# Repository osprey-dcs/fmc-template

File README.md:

# RF Input FMC

A single width HPC FMC board which brings in two high frequency (RF) clocks to
to MGT capable pins when matched with the [LBL Marble](https://github.com/BerkeleyLab/Marble) FMC carrier.

This design is Open Hardware created by Osprey DCS and published under the terms of the
[CERN Open Hardware Licence Version 2 - Strongly Reciprocal](cern_ohl_s_v2.txt) license.

This repository contains KiCad 9 design files.

- [Current generated](https://osprey-dcs.github.io/fmc-template/)
  - [Schematic](https://osprey-dcs.github.io/fmc-template/fmc-template-schematic.pdf)
  - [BoM](https://osprey-dcs.github.io/fmc-template/fmc-template-bom.csv)
  - [STeP model](https://osprey-dcs.github.io/fmc-template/3D/fmc-template-3D.step)

## Status

Incomplete, under development, and not yet produced.

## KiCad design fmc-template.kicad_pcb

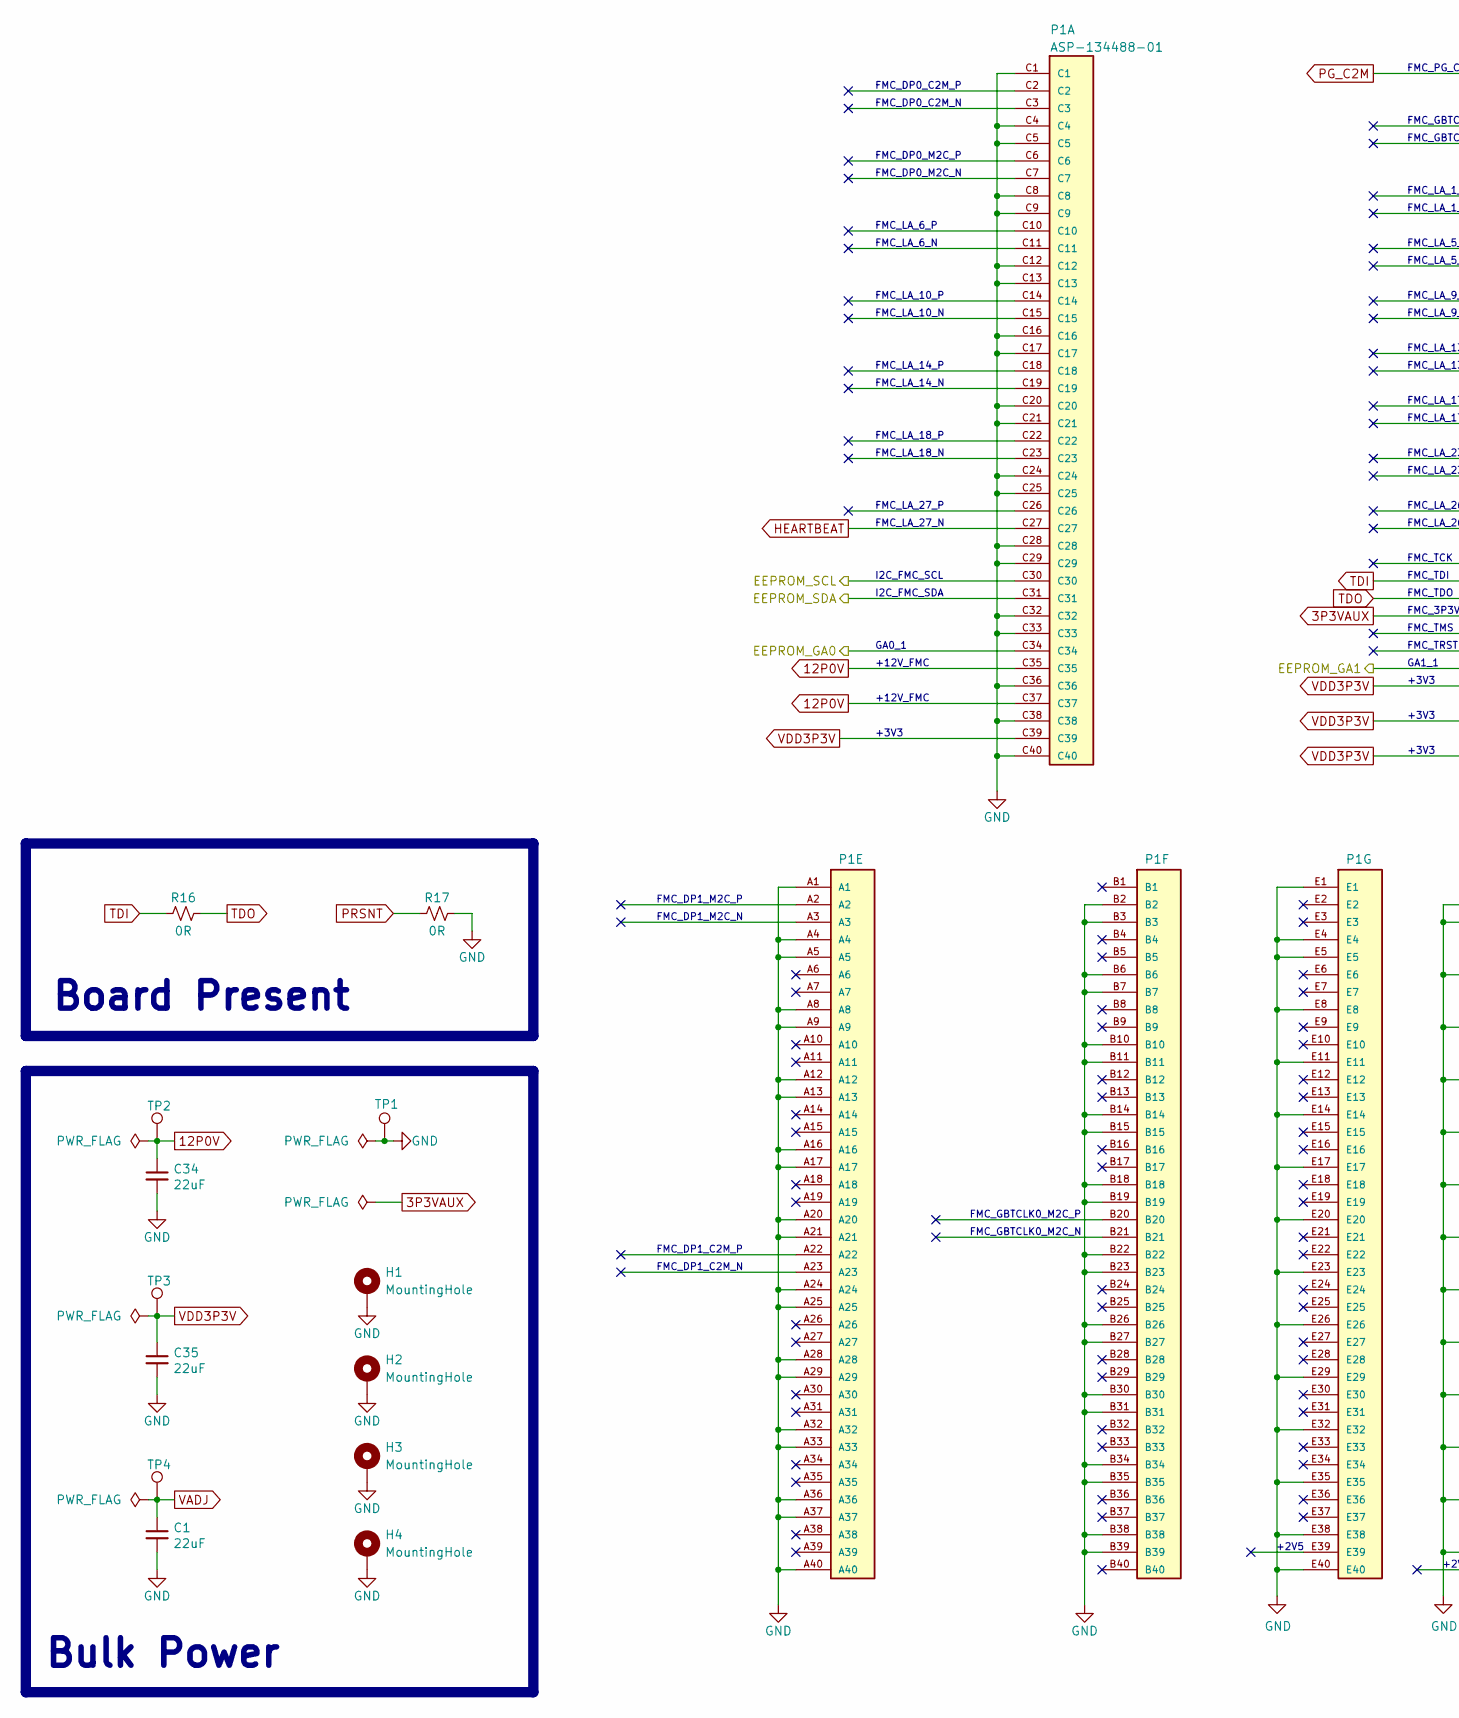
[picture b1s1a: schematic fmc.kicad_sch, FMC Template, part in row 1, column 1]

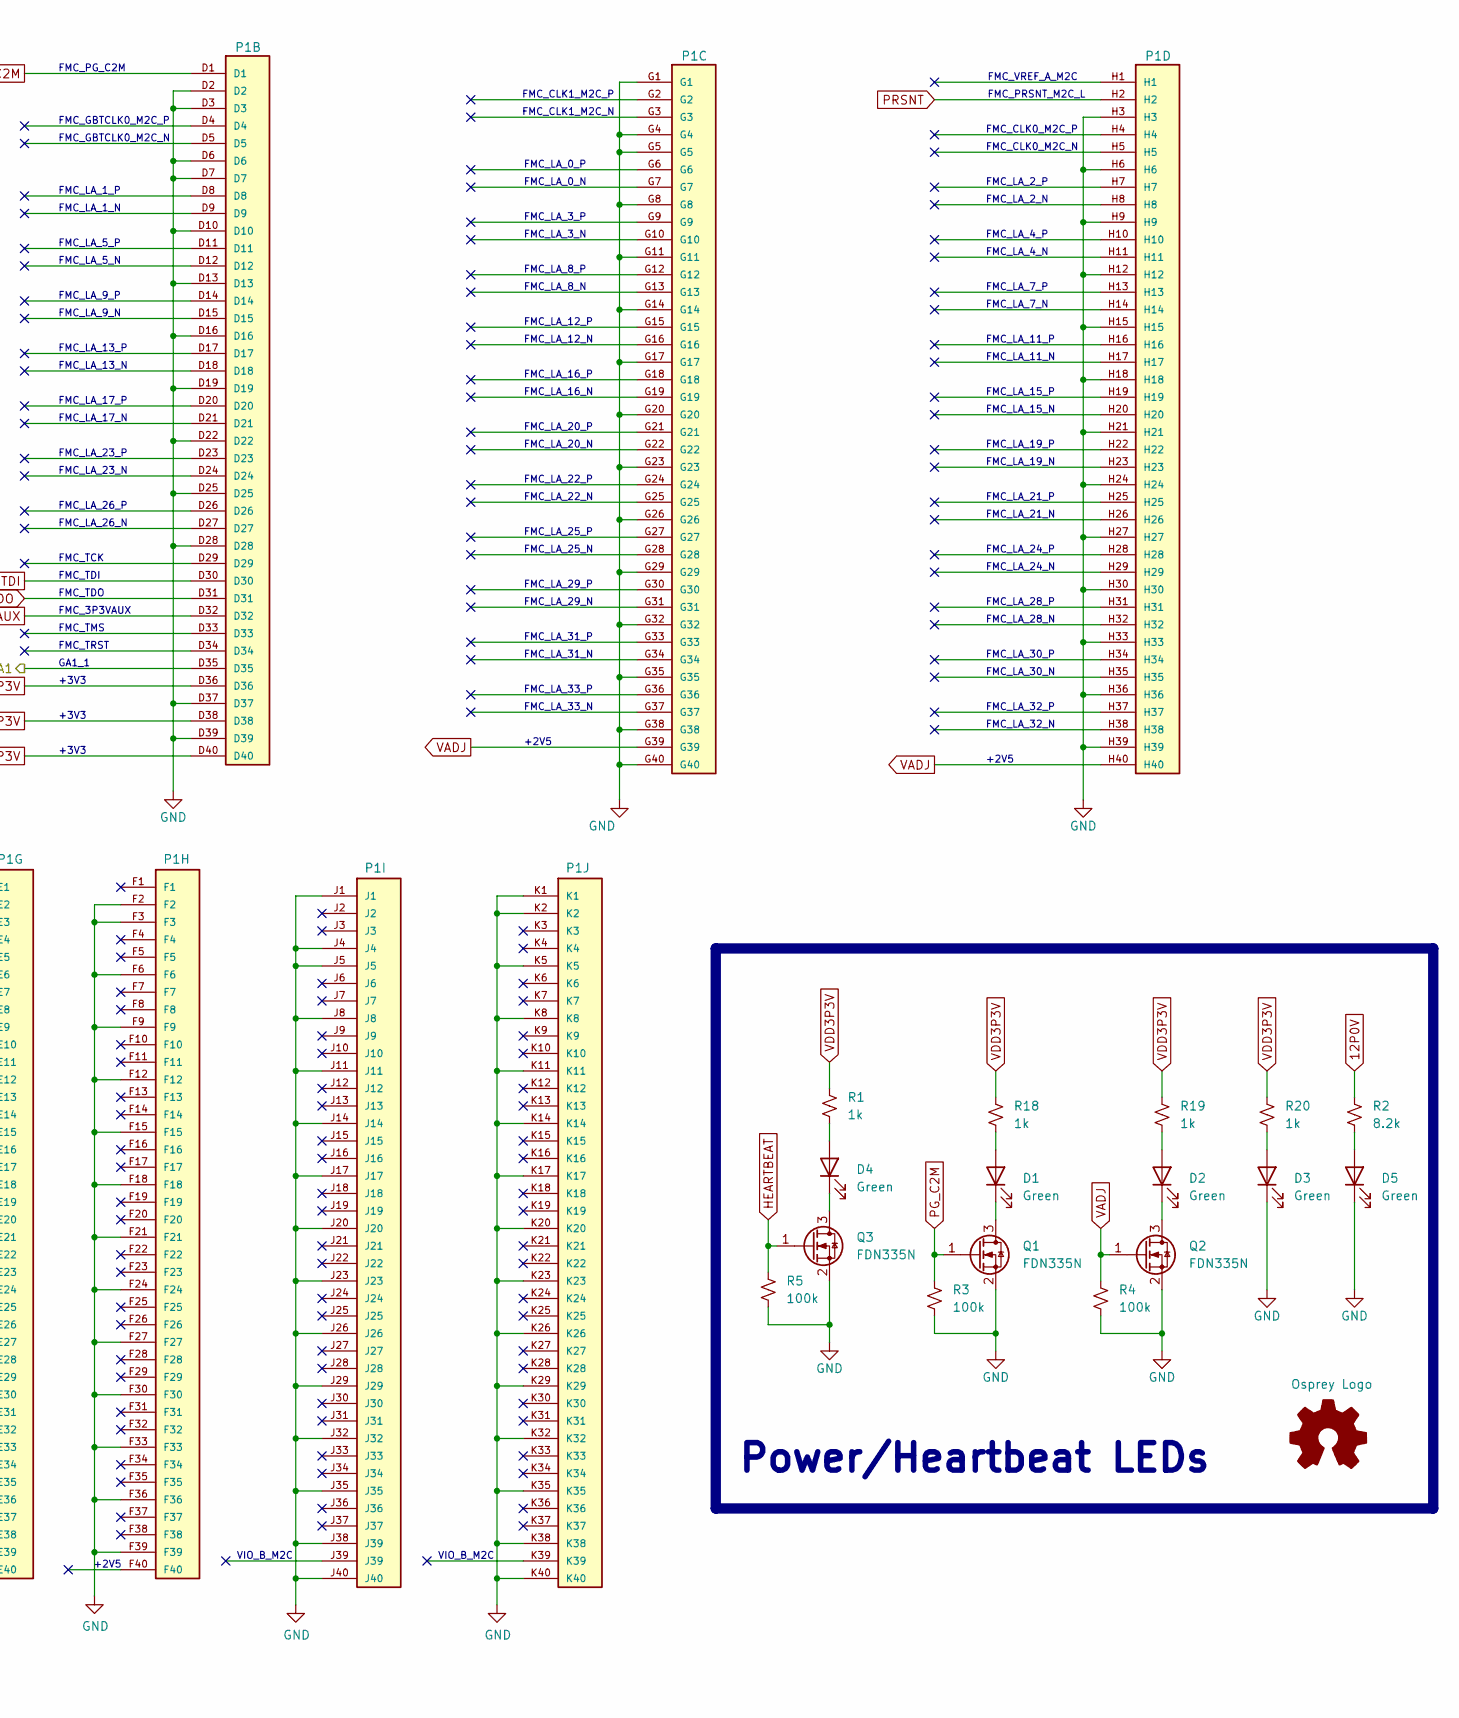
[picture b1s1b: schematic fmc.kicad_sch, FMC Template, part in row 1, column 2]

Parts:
C1, C34, C35: 22uF; C_1210_3225Metric; MPN MSASG32MSB5226MPNA01
D1, D2, D3, D4, D5: Green; LED_0603_1608Metric; MPN APT1608CGCK
H1, H2: MountingHole; MountingHole_3.0mm_M2.5_Pad_3.3mm_MarbleSlot
H3, H4: MountingHole; MountingHole_3.0mm_3.8mm_Pad_3.3mm_MarbleSlot
Logo1: Osprey Logo; Logo_2X
P1: ASP-134488-01; Samtec_FMC_ASP-134602-01_10x40_P1.27mm_Vertical; MPN ASP-134488-01
Q1, Q2, Q3: FDN335N; SOT-23; MPN FDN335N
R1, R18, R19, R20: 1k; R_0603_1608Metric; MPN ESR03EZPF1001
R2: 8.2k; R_0603_1608Metric; MPN ESR03EZPF8201
R3, R4, R5: 100k; R_0603_1608Metric; MPN ESR03EZPF1003
R16, R17: 0R; R_0603_1608Metric; MPN ERJ-3GEY0R00V
TP1: Keystone5001; TestPoint_Keystone_5000-5004_Miniature; MPN 5001
TP2, TP3, TP4: Keystone5000; TestPoint_Keystone_5000-5004_Miniature; MPN 5000

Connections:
3P3VAUX: P1.D32; also elsewhere on the board
12P0V: C34.1, P1.C35, P1.C37, R2.2, TP2.1
/EEPROM/GA0: P1.C34; also elsewhere on the board
/EEPROM/GA1: P1.D35; also elsewhere on the board
/EEPROM/SCL: P1.C30; also elsewhere on the board
/EEPROM/SDA: P1.C31; also elsewhere on the board
GND: C1.2, C34.2, C35.2, D3.1 (K), D5.1 (K), H1.1, H2.1, H3.1, H4.1, P1.A1, P1.A4, P1.A5, P1.A8, P1.A9, P1.A12, P1.A13, P1.A16, P1.A17, P1.A20, P1.A21, P1.A24, P1.A25, P1.A28, P1.A29, P1.A32, P1.A33, P1.A36, P1.A37, P1.A40, P1.B2, P1.B3, P1.B6, P1.B7, P1.B10, P1.B11, P1.B14, P1.B15, P1.B18, P1.B19, P1.B22, P1.B23, P1.B26, P1.B27, P1.B30, P1.B31, P1.B34, P1.B35, P1.B38, P1.B39, P1.C1, P1.C4, P1.C5, P1.C8, P1.C9, P1.C12, P1.C13, P1.C16, P1.C17, P1.C20, P1.C21, P1.C24, P1.C25, P1.C28, P1.C29, P1.C32, P1.C33, P1.C36, P1.C38, P1.C40, P1.D2, P1.D3, P1.D6, P1.D7, P1.D10, P1.D13, P1.D16, P1.D19, P1.D22, P1.D25, P1.D28, P1.D37, P1.D39, P1.E1, P1.E4, P1.E5, P1.E8, P1.E11, P1.E14, P1.E17, P1.E20, P1.E23, P1.E26, P1.E29, P1.E32, P1.E35, P1.E38, P1.E40, P1.F2, P1.F3, P1.F6, P1.F9, P1.F12, P1.F15, P1.F18, P1.F21, P1.F24, P1.F27, P1.F30, P1.F33, P1.F36, P1.F39, P1.G1, P1.G4, P1.G5, P1.G8, P1.G11, P1.G14, P1.G17, P1.G20, P1.G23, P1.G26, P1.G29, P1.G32, P1.G35, P1.G38, P1.G40, P1.H3, P1.H6, P1.H9, P1.H12, P1.H15, P1.H18, P1.H21, P1.H24, P1.H27, P1.H30, P1.H33, P1.H36, P1.H39, P1.J1, P1.J4, P1.J5, P1.J8, P1.J11, P1.J14, P1.J17, P1.J20, P1.J23, P1.J26, P1.J29, P1.J32, P1.J35, P1.J38 (J39), P1.J40, P1.K1, P1.K2, P1.K5, P1.K8, P1.K11, P1.K14, P1.K17, P1.K20, P1.K23, P1.K26, P1.K29, P1.K32, P1.K35, P1.K38, P1.K40, Q1.2 (S), Q2.2 (S), Q3.2 (S), R3.1, R4.1, R5.1, R17.2, TP1.1; also elsewhere on the board
HEARTBEAT: P1.C27, Q3.1 (G), R5.2
unnamed: D1.2 (A), R18.1
unnamed: D1.1 (K), Q1.3 (D)
unnamed: D2.2 (A), R19.1
unnamed: D2.1 (K), Q2.3 (D)
unnamed: D3.2 (A), R20.1
unnamed: D4.2 (A), R1.1
unnamed: D4.1 (K), Q3.3 (D)
unnamed: D5.2 (A), R2.1
PG_C2M: P1.D1, Q1.1 (G), R3.2
PRSNT: P1.H2, R17.1
TDI: P1.D30, R16.2
TDO: P1.D31, R16.1
VADJ: C1.1, P1.G39, P1.H40, Q2.1 (G), R4.2, TP4.1
VDD3P3V: C35.1, P1.C39, P1.D36, P1.D38, P1.D40, R1.2, R18.2, R19.2, R20.2, TP3.1

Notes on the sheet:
FMC_LA_19_N
FMC_GBTCLK0_M2C_N
FMC_LA_3_P
FMC_LA_5_P
FMC_LA_32_P
FMC_CLK0_M2C_P
VIO_B_M2C
FMC_LA_4_P
FMC_LA_26_N
FMC_LA_20_P
FMC_LA_21_N
FMC_LA_29_N
FMC_LA_14_N
FMC_LA_21_P
FMC_LA_22_P
FMC_LA_18_N
FMC_3P3VAUX
FMC_LA_6_P
FMC_LA_19_P
FMC_LA_7_N
FMC_LA_30_P
Power/Heartbeat LEDs
+2V5
FMC_VREF_A_M2C
FMC_CLK0_M2C_N
FMC_LA_9_N
FMC_LA_2_N
FMC_LA_16_P
FMC_LA_31_P
FMC_LA_10_N
+3V3
FMC_LA_14_P
FMC_LA_32_N
GA0_1
FMC_LA_1_P
FMC_DP1_M2C_P
FMC_TDI
+3V3
FMC_LA_11_P
FMC_DP0_C2M_P

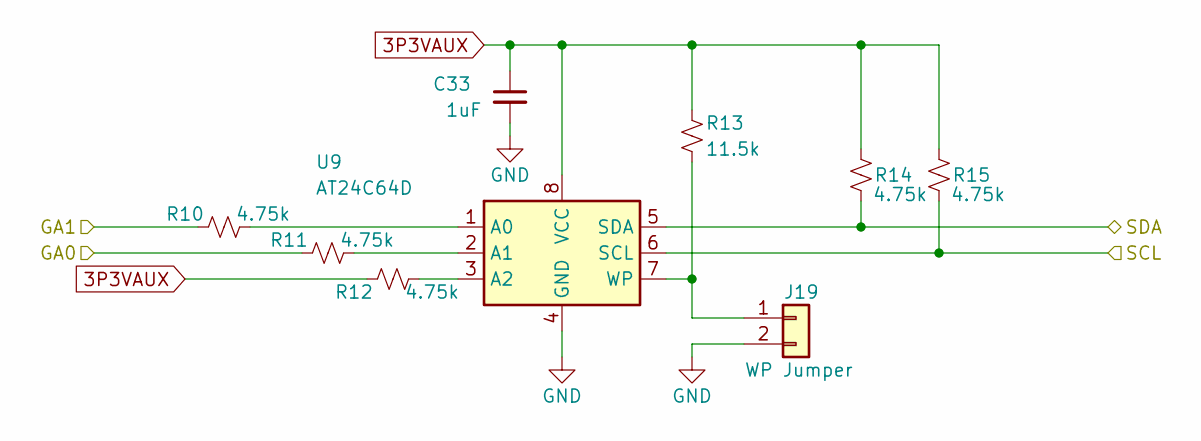
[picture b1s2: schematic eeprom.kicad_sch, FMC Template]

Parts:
C33: 1uF; C_0603_1608Metric; MPN GCM188R71E105KA64D
J19: WP Jumper; PinHeader_1x02_P2.54mm_Vertical; MPN M20-9990245
R10, R11, R12, R14, R15: 4.75k; R_0603_1608Metric; MPN RC0603FR-134K75L
R13: 11.5k; R_0603_1608Metric; MPN RC0603FR-0711K5L
U9: AT24C64D; SOIC-8_3.9x4.9mm_P1.27mm; MPN AT24C64D-SSHM-T

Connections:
3P3VAUX: C33.1, R12.1, R13.1, R14.1, R15.1, U9.8 (VCC); also elsewhere on the board
/EEPROM/GA0: R11.1; also elsewhere on the board
/EEPROM/GA1: R10.1; also elsewhere on the board
/EEPROM/SCL: R15.2, U9.6 (SCL); also elsewhere on the board
/EEPROM/SDA: R14.2, U9.5 (SDA); also elsewhere on the board
GND: C33.2, J19.2, U9.4 (GND); also elsewhere on the board
unnamed: J19.1, R13.2, U9.7 (WP)
unnamed: R10.2, U9.1 (A0)
unnamed: R11.2, U9.2 (A1)
unnamed: R12.2, U9.3 (A2)

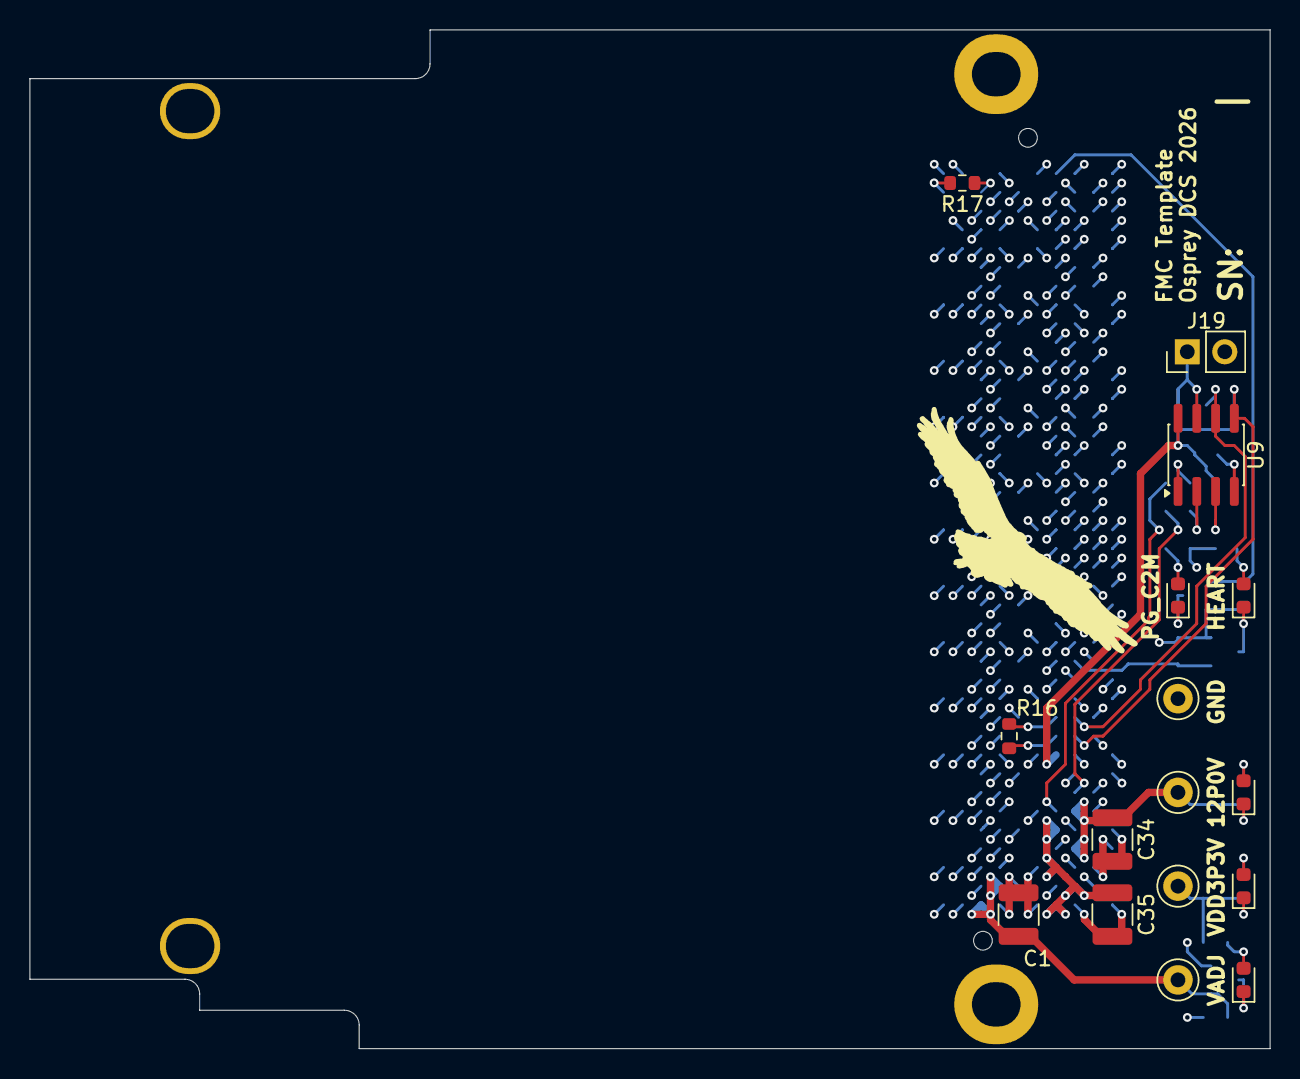
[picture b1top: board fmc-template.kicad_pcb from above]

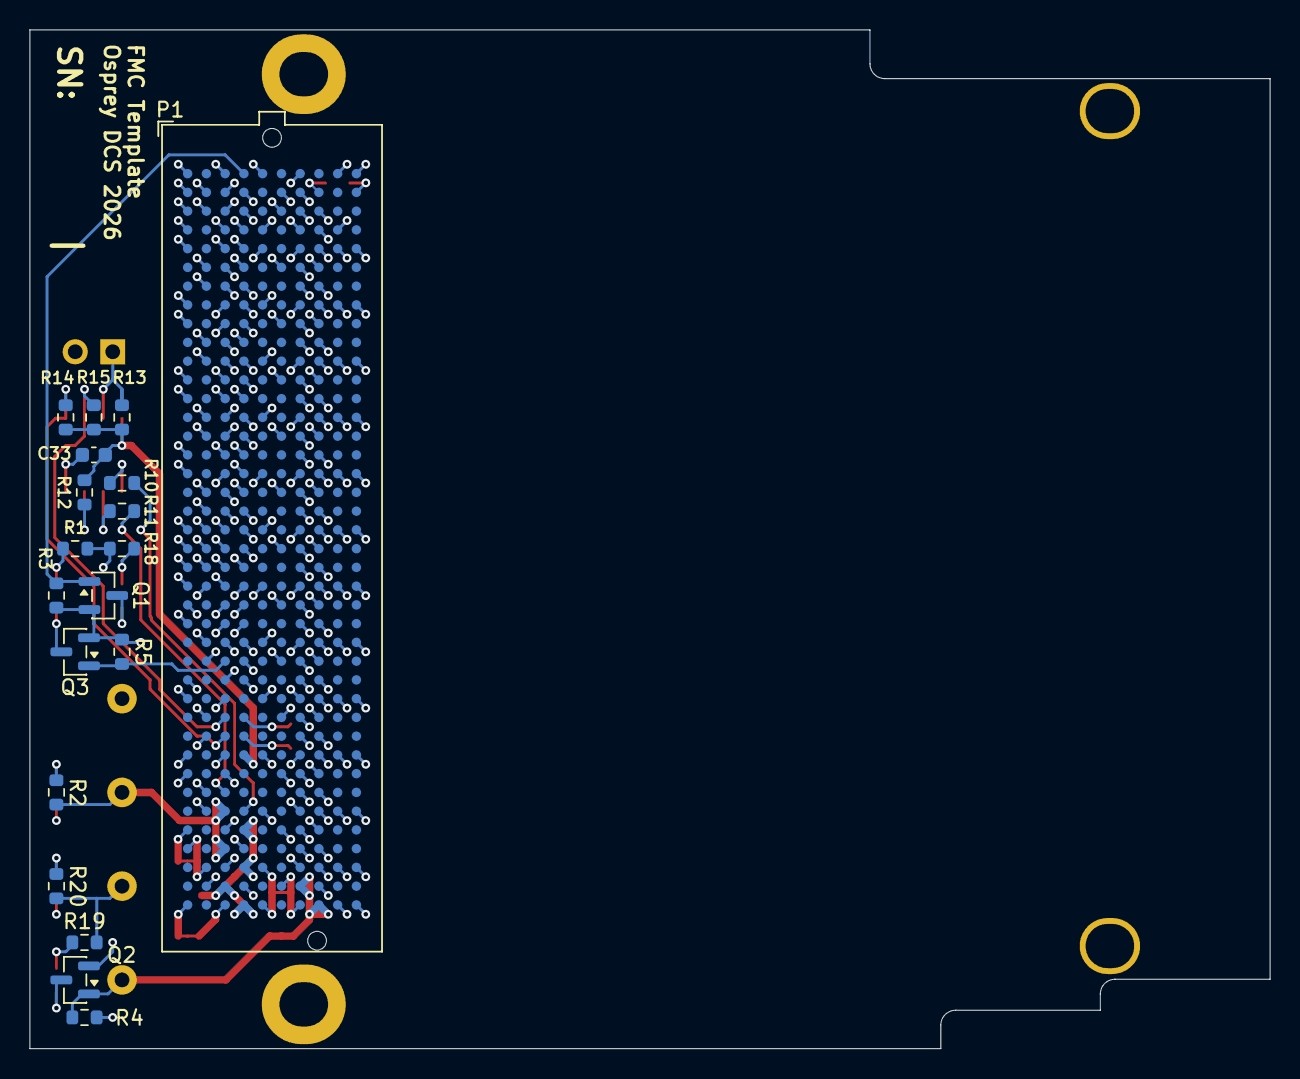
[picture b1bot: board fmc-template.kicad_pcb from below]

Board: 6 copper layers, 84.0 x 69.0 mm, 40 parts (19 on the bottom side), 26 nets.

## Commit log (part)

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2026-03-14 Started FMC Template
    - Ready to use
    - Some cleanup of unused libraries may still be needed
2026-05-07 Changed layout, added 12V and Heart LEDs
2026-05-18 Add slotted mounting hole footprints for marble alignment
2026-05-18 add kibot
2026-05-18 fix instance names
2026-05-18 Fix eeprom labels and connect FMC_LA_5_P
    Change eeprom local to hierarchical label.
    Connect D11 to FMC_LA_5_P label
2026-05-18 update pcb from sch
2026-05-18 README

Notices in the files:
eeprom.kicad_sch:
SPDX-FileCopyrightText: 2025 Osprey DCS
SPDX-License-Identifier: CERN-OHL-S-2.0+
